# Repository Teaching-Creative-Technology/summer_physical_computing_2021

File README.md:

# Modes + Models of Synchronization
[tbd]

## Physical Computing 2021
SoSe 2021 Physical Computing at HS Magdeburg

* 16.04.2021 – VL / Intro + Organisatorisches 
* 23.04.2021 – VL / Basics 1 
* 30.04.2021 – VL / Basics 2 
* 07.05.2021 – VL / Basics 3 
* 14.05.2021 – Entfällt (Christi Himmelfahrt)  
* 21.05.2021 – VL / Basics 4 
* 28.05.2021 – VL / Basics 5 
* 04.06.2021 – VL / Basics 6 
* 11.06.2021 – VL / Special Topics 1 
* 18.06.2021 – VL / Special Topics 2 
* 25.06.2021 – VL / Special Topics 3 
* 02.07.2021 – Konsultationen Individual-Slots (ca. 10min. pro Slot / 9 Studenten in 90min) 
* 09.07.2021 – Konsultationen Individual-Slots (ca. 10min. pro Slot / 9 Studenten in 90min) 
* 16.07.2021 – Konsultationen Individual-Slots (ca. 10min. pro Slot / 9 Studenten in 90min) 
* 23.07.2021 – Präsentationen (Pre-Recorded) + Ende der Vorlesungszeit 
* 30.09.2021 – Semesterende

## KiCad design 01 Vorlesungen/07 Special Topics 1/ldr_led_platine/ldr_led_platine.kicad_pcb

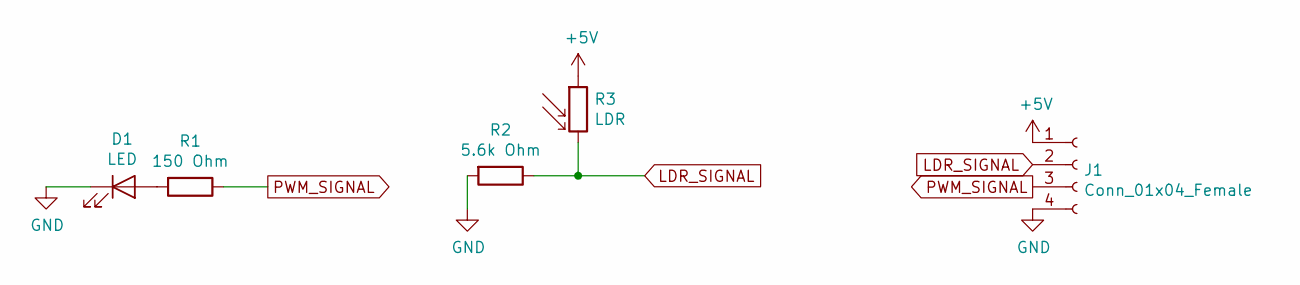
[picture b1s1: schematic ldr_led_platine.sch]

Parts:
D1: LED; LED_D5.0mm
J1: Conn_01x04_Female; TerminalBlock_Phoenix_MKDS-3-4-5.08_1x04_P5.08mm_Horizontal
R1: 150 Ohm; R_Axial_DIN0309_L9.0mm_D3.2mm_P12.70mm_Horizontal
R2: 5.6k Ohm; R_Axial_DIN0309_L9.0mm_D3.2mm_P12.70mm_Horizontal
R3: LDR; R_LDR_4.9x4.2mm_P2.54mm_Vertical

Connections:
+5V: J1.1, R3.1
GND: D1.1 (K), J1.4, R2.2
LDR_SIGNAL: J1.2, R2.1, R3.2
unnamed: D1.2 (A), R1.2
PWM_SIGNAL: J1.3, R1.1

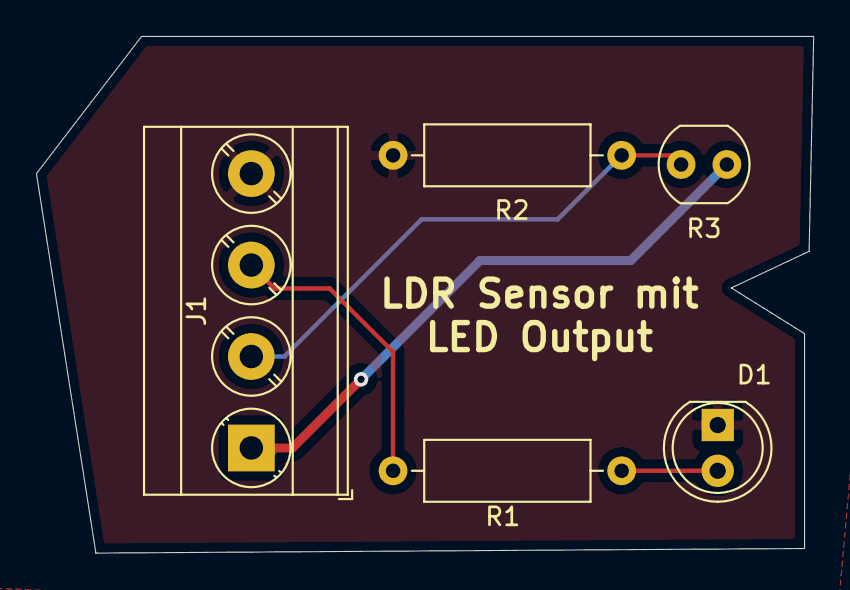
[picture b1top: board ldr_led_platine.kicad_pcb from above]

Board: 2 copper layers, 43.2 x 28.7 mm, 5 parts (0 on the bottom side), 5 nets.

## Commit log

2021-04-16 init
2021-04-16 readme
2021-04-16 dates as list
2021-04-23 added basics 1
    elektrizität: strom, spannung, widerstand
    ohmsches gesetz
    leistung
    sicherheitsregeln
    stromkreise
    schaltpläne
2021-04-30 added basics 2
    Recap + Zusatz
    Schaltzeichen + Bauteile
    Datenblätter
    Grundschaltungen 2
    Arduino Basics
    Arduino Typen
2021-05-07 added basics 3
    Recap
    Warum Physical Computing?
    Arduino Bauteile
    EVA-Prinzip
    Aufgabe 2
2021-05-07 abgaben aufgabe 1
2021-05-21 basics 4
    arduino bauteile
    shields
    bibliotheken
    multitasking
    workshop servos + code
2021-05-28 added basics 5
    transistors + finite state machine
2021-06-04 Basics 6
    Multimeter
    Arduino Kommunikation (UART, I2C, SPI)
    MQTT
2021-06-11 special topics 1 - pcb design
